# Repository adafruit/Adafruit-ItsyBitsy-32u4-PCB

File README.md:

## Adafruit ItsyBitsy 32u4 PCB

<a href="http://www.adafruit.com/products/3677">&nbsp; 
<a href="http://www.adafruit.com/products/3675"><br/>
Click picture or links below to purchase one from the Adafruit shop</a>

PCB CAD files for the Adafruit ItsyBitsy 32u4. PCB format is EagleCAD schematic and board layout

For more details, check out the product pages at
* ItsyBitsy 32u4 - 5V 16MHz https://www.adafruit.com/products/3677
* ItsyBitsy 32u4 - 3V 8MHz https://www.adafruit.com/products/3675

### Description

What's smaller than a Feather but larger than a Trinket? It's an ItsyBitsy! Small, powerful, Arduino-compatible - this microcontroller board is perfect when you want something very compact, but still with a bunch of pins.

ItsyBitsy is only 1.4" long by 0.7" wide, but has 6 power pins, 6 analog & digital pins and 17 digital pins. It packs much of the same capability as an Arduino UNO. So it's great once you've finished up a prototype on a bigger Arduino, and want to make the project much smaller.

The ItsyBitsy 32u4 5V 16MHz and 3V 8MHz use the Atmega32u4 chip, which is the same core chip in the Arduino Leonardo as well as the same chip we use in our Feather 32u4. You'll be happy to hear that not only is ItsyBitsy programmable using the Arduino IDE as you already have set up, but a vast number of Arduino projects will work out of the box!

We recommend this as an upgrade from the Pro Trinket 5V/3V because they has native USB so it will work with all computers, USB serial debugging, and a more reliable bootloader.

### License

Adafruit invests time and resources providing this open source design, please support Adafruit and open-source hardware by purchasing products from [Adafruit](https://www.adafruit.com)!

Designed by Limor Fried/Ladyada for Adafruit Industries.

Creative Commons Attribution/Share-Alike, all text above must be included in any redistribution. See license.txt for additional details.

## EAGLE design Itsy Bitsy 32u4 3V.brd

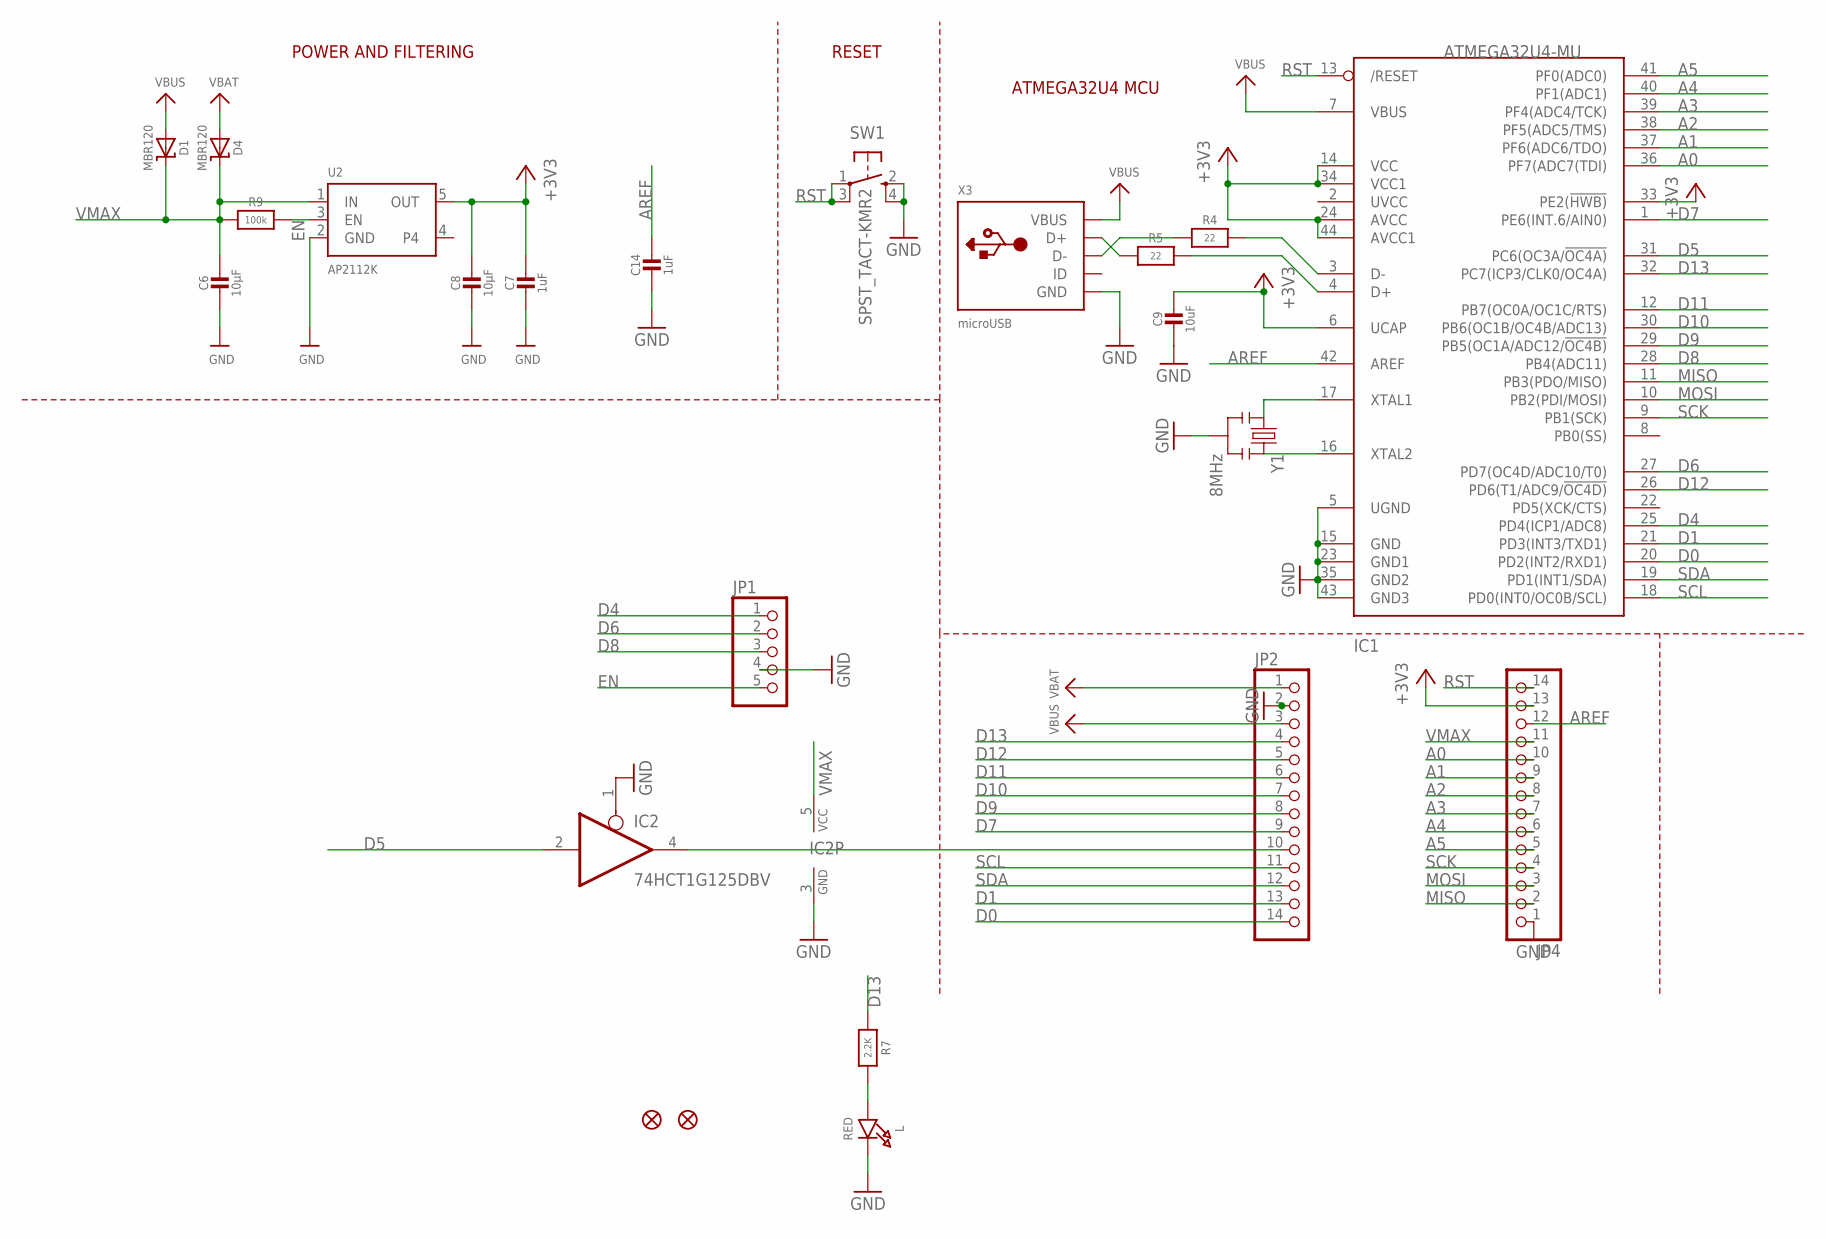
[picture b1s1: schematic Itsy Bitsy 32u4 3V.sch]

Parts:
C6, C8: 10µF; 0805-NO
C7, C14: 1uF; 0603-NO
C9: 10uF; 0805-NO
D1, D4: MBR120; SOD-123
IC1: ATMEGA32U4-MU; TQFN44_7MM
IC2: 74HCT1G125DBV; SOT23-5
JP1: HEADER-1X5ROUND; 1X05_ROUND
JP2, JP4: HEADER-1X14; 1X14_ROUND70
L: RED; CHIPLED_0805_NOOUTLINE
R4, R5: 22; 0603-NO
R7: 2.2K; 0603-NO
R9: 100k; 0603-NO
SW1: SPST_TACT-KMR2; KMR2
U2: AP2112K; SOT23-5
U$34, U$35: FIDUCIAL""; FIDUCIAL_1MM
X3: microUSB; 4UCONN_20329_V2
Y1: 8MHz; RESONATOR-SMD

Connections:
+3V3: C7.1, C8.1, C9.1, IC1.6 (UCAP), IC1.14 (VCC), IC1.24 (AVCC), IC1.33 (PE2(!HWB)), IC1.34 (VCC1), IC1.44 (AVCC1), JP4.13, U2.5 (OUT)
A0: IC1.36 (PF7(ADC7(TDI)), JP4.10
A1: IC1.37 (PF6(ADC6/TDO)), JP4.9
A2: IC1.38 (PF5(ADC5/TMS)), JP4.8
A3: IC1.39 (PF4(ADC4/TCK)), JP4.7
A4: IC1.40 (PF1(ADC1)), JP4.6
A5: IC1.41 (PF0(ADC0)), JP4.5
AREF: C14.1, IC1.42 (AREF), JP4.12
D0: IC1.20 (PD2(INT2/RXD1)), JP2.14
D1: IC1.21 (PD3(INT3/TXD1)), JP2.13
D4: IC1.25 (PD4(ICP1/ADC8)), JP1.1
D5: IC1.31 (PC6(OC3A/!OC4A)), IC2.2 (I)
D5_OUT: IC2.4 (O), JP2.10
D6: IC1.27 (PD7(OC4D/ADC10/T0)), JP1.2
D7: IC1.1 (PE6(INT.6/AIN0)), JP2.9
D8: IC1.28 (PB4(ADC11)), JP1.3
D9: IC1.29 (PB5(OC1A/ADC12/!OC4B)), JP2.8
D10: IC1.30 (PB6(OC1B/OC4B/ADC13)), JP2.7
D11: IC1.12 (PB7(OC0A/OC1C/RTS)), JP2.6
D12: IC1.26 (PD6(T1/ADC9/!OC4D)), JP2.5
D13: IC1.32 (PC7(ICP3/CLK0/OC4A)), JP2.4, R7.1
D+: IC1.4 (D+), R5.2
D-: IC1.3 (D-), R4.2
EN: JP1.5, R9.2, U2.3 (EN)
GND: C6.2, C7.2, C8.2, C9.2, C14.2, IC1.5 (UGND), IC1.15 (GND), IC1.23 (GND1), IC1.35 (GND2), IC1.43 (GND3), IC2.1 (OE), IC2.3 (GND), JP1.4, JP2.2, JP4.1, L.C, SW1.2 (S), SW1.4 (S1), U2.2 (GND), X3.BASE@1 (GND), X3.BASE@2 (GND), X3.GND, X3.SPRT@1 (GND), X3.SPRT@2 (GND), X3.SPRT@3 (GND), X3.SPRT@4 (GND), Y1.2
MISO: IC1.11 (PB3(PDO/MISO)), JP4.2
MOSI: IC1.10 (PB2(PDI/MOSI)), JP4.3
unnamed: L.A, R7.2
unnamed: IC1.16 (XTAL2), Y1.3
unnamed: IC1.17 (XTAL1), Y1.1
unnamed: R5.1, X3.D+
unnamed: R4.1, X3.D-
RST: IC1.13 (/RESET), JP4.14, SW1.1, SW1.3 (P1)
SCK: IC1.9 (PB1(SCK)), JP4.4
SCL: IC1.18 (PD0(INT0/OC0B/SCL)), JP2.11
SDA: IC1.19 (PD1(INT1/SDA)), JP2.12
VBAT: D4.A, JP2.1
VBUS: D1.A, IC1.7 (VBUS), JP2.3, X3.VBUS
VMAX: C6.1, D1.C, D4.C, IC2.5 (VCC), JP4.11, R9.1, U2.1 (IN)

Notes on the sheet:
POWER AND FILTERING
RESET
ATMEGA32U4 MCU

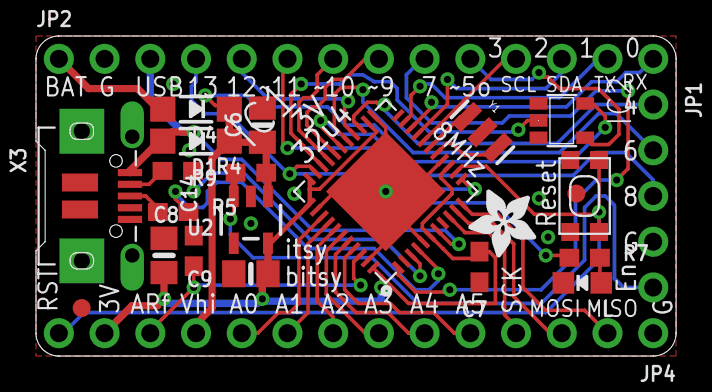
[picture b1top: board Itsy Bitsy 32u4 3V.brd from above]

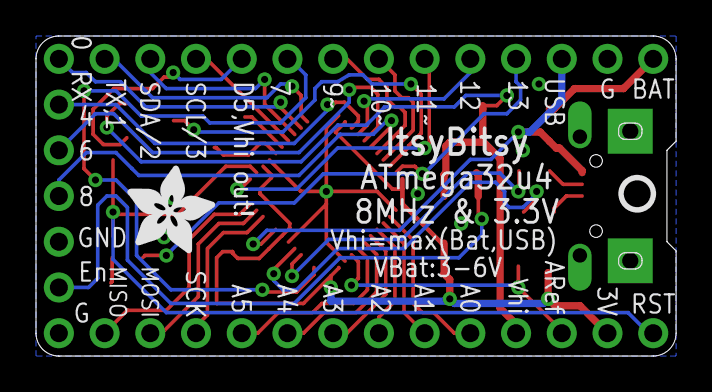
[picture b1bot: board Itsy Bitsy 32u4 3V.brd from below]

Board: 2 copper layers, 35.6 x 17.8 mm, 26 parts (2 on the bottom side), 39 nets.

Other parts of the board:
U$2: PCBFEAT-REV-040
U$4: ADAFRUIT_5MM
U$7: ADAFRUIT_3.5MM

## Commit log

2018-01-02 itsy bitsy 32u4 files!
2022-04-13 Added PrettyPins
2025-05-05 update 3V regulator label

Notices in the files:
parts and their libraries:
microbuilder: This work is placed in the public domain, and may be freely used for commercial and non-commercial work with the following conditions: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
SparkFun: Licensing: CC v3.0 Share-Alike You are welcome to use this library for commercial purposes.
